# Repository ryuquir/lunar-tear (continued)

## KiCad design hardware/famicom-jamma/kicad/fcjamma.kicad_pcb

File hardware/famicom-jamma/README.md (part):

# ファミコン JAMMA 基板　回路設計（rev 0.3）

日本のファミリーコンピュータ（HVC-001）の CPU（RP2A03）と PPU（RP2C02）を載せ替えて、JAMMA 筐体で動かす基板の設計データです。
調査結果は `reports/ファミコン JAMMA 基板 仕様調査.md`、ユーザー要求は `research_notes/ファミコン JAMMA 基板 仕様調査/user_requirements.md` にあります。

部品の実装はすべて JLCPCB に任せます。自分ではんだ付けする部品はありません。
基板が届いたあとの作業は、ドナー機から外した CPU と PPU をソケットに挿すことと、USB でファームウェアを書くことだけです。

| 版 | 内容 | 場所 |
|---|---|---|
| rev 0.1 | JLCPCB は Basic 部品だけを実装。残りは秋月電子の部品を手はんだ（はんだ付け 約 650 か所） | コミット `35126bd` |
| rev 0.2 | JLCPCB がすべて実装（Extended 部品も使う）。手はんだ 0 か所。独立レビューの前の版 | コミット `ae6575b` |
| **rev 0.3** | **rev 0.2 に独立レビューの指摘を反映した版（6 章）** | この版 |

## 1. 現在の状態

| 段階 | 内容 | 状態 |
|---|---|---|
| 1 | 回路設計（部品の確定、ピン割り当て、回路図、ネットリスト、独立レビュー） | **この版** |
| 2 | フットプリント作成（JAMMA の金フィンガー、60 ピン端子、半固定抵抗など）と部品配置 | **2-1 自作フットプリント: 完了**（`design/footprints.py`。部品用 5 種は 2026-11-15、捨て基板のミシン目と治具穴は 2026-11-16）。**2-2a 基板の外形・捨て基板・取り付け穴・位置合わせマーク・基板の設定: 完了**（`design/board.py` → `kicad/fcjamma.kicad_pcb`、2026-11-16。レビューを受けて同日修正）。2-2b 部品の配置: カセット端子のサンプルと JLCPCB の回答を待つ（配置の案は `mech/board_outline_plan.png`） |
| 3 | 配線、DRC、JLCPCB 向けの製造データ（ガーバー、部品表、座標） | 未着手 |
| 4 | ファームウェア（Pico 2 ×3） | 未着手 |

この版は机上の設計です。実物での動作確認はまだ 1 つもありません。未実証の点は 7 章にまとめています。
段階 3 が終わるまで、この基板は発注できません。
段階 2 の部品配置（2-2）を始める前に済ませることが 2 つあります（8 章）。カセット端子のサンプルでの勘合確認と、JLCPCB への事前質問です。
どちらも依頼者が承認し（2026-11-14）、発注代行（GrokBOT）に頼む文書を Google ドライブの「異能ソフト／ファミコンアーキテクチャー基盤」に置いています。
その結果に左右されない自作フットプリント（2-1）は先に作りました。寸法と出典は `research_notes/ファミコン JAMMA 基板 仕様調査/footprint_specs.md` にあります。
マイコンは Pico 2 のまま進めます（2026-11-15 に決定）。素のチップ（RP2350）に替える案は、調べた結果を `research_notes/ファミコン JAMMA 基板 仕様調査/rp2350_bare_chip_feasibility.md` に残し、次の版で改めて検討します。

## 2. ファイルと作り方

| 場所 | 内容 |
|---|---|
| `design/circuit.py` | 回路の記述（部品、ネット、定数、設計意図の注記）。**これが正本** |
| `design/symbols.py` | KiCad 標準ライブラリにない部品の記号（ピン番号と名前） |
| `design/footprints.py` | 基板の自作フットプリント 7 種（部品用 5 種と、捨て基板のミシン目・治具穴。寸法と出典、ビルドが確かめる事実）と基板の規則。`kicad/fcjamma.pretty` と `kicad/fcjamma.kicad_dru` はここから作る |
| `tools/build.py` | 回路の記述から KiCad プロジェクトを作り、検査し、費用を計算する |
| `tools/jlc_parts.py` | Extended 部品の在庫・価格・実装区分・X 線検査の要否を JLCPCB から取り直す |
| `tools/check_footprints.py` | 自作フットプリントを KiCad 自身（システムの Python の pcbnew）に読ませ、生成器が書いたとおりに読めるか（パッドの位置・大きさ・形・角度・穴・層、禁止域の層と規則、図形と文字の位置、属性）を確かめる（`build.py` が呼ぶ） |
| `tools/check_rules.py` | 基板の規則（`kicad/fcjamma.kicad_dru`）が効くことを試験用の基板で確かめる。禁止の場所に置いた 21 個の試し（ビア、線、パッド、マスクの開口、シルク、小さな部品、穴どうしの間隔、環幅、SMD のパッドの間隔、外形線の無い部品）がそれぞれの規則に引っかかること（規則ごとに 1 つ以上。値のある規則は限界のすぐ内側の試しに引っかかり、すぐ外側の 5 個には引っかからない。値を緩めても厳しくしても分かる）、回路と基板が使う 42 種のフットプリントを 1 つずつ、回路のネットを付けて並べた基板は規則に 1 つも触れないこと（`build.py` が呼ぶ） |
| `tools/fcgen/` | 生成器（回路モデル、部品ヘルパー、KiCad 出力） |
| `tools/setup_env.sh` | 作業環境の準備（KiCad 10 と Python 環境） |
| `data/jlcpcb_basic_parts_2026-11-10.csv` | JLCPCB の Basic 部品 351 件 |
| `data/jlcpcb_extended_parts.csv` | この基板が使う Extended 部品 18 種の在庫・価格・実装区分（取得日つき） |
| `kicad/` | 生成された KiCad 10 プロジェクト（手で編集しない）。ビルドは作業用のフォルダでプロジェクト全体（回路図、記号、フットプリント、基板の規則、基板）を作って検査し、基板も含めてすべて通ったときだけ、生成したファイルを `kicad/` で入れ替える（KiCad の設定・履歴（`.history`）・自動保存などのファイルや、生成していないファイルには触らない）。通らなかったときは `kicad/` と `out/board/` は前に通ったままで、通らなかったプロジェクトは `out/failed/kicad/` に残る。pcbnew が無くて基板を検査できなかったときも `kicad/` は変えず、プロジェクトは `out/unchecked/kicad/` に残る（どちらも git には入れない） |
| `out/` | 回路図 PDF、ネットリスト、部品表、ERC の結果、費用の内訳（`cost_estimate.csv`）。`out/board/` を除き、通らなかったビルドでもそのビルドの内容に書き直される（そのときは `out/failed/kicad/` と合い、`kicad/` とは合わない）。`ordering/make_grok_package.py` は、`out/failed/` か `out/unchecked/` があると止まる |
| `out/footprints/` | 自作フットプリントの図（SVG）と一覧の画像（`footprints_overview.png`）、カセット端子の実寸の確認用紙（`J8_cartridge_slot_1to1_check.pdf`、A4 横、倍率 100 % で印刷） |
| `mech/` | 基板の外形と部品配置の案（`floorplan.py` が重なりを検査してから図を描く）。寸法は `design/board.py` と同じであることをビルドが確かめる |
| `design/board.py` | 基板そのもの（外形、JAMMA のタングとキー溝、捨て基板とミシン目、取り付け穴、治具穴、位置合わせマーク、積層、原点、出力の設定）。`kicad/fcjamma.kicad_pcb` はここから作る |
| `tools/make_board.py` | `design/board.py` から KiCad の基板ファイルを作り、読み直して実測する（タングとキー溝の寸法と位置、タングの横に基板が無いこと、外形の角と溝の形、フィンガーの範囲、J1 の全ピンのネットと回路図とのつながり、穴、捨て基板・つなぎ・ミシン目、治具穴、位置合わせマーク、外形線の有無、積層、出力の設定、縁から部品までの距離など 142 項目。限界値はコネクタの図面と JLCPCB の値を書き直したもの。`build.py` がシステムの Python で呼び、作業用のフォルダのプロジェクトの中で DRC と回路図との照合までかける。ビルド全体が通ったときだけ、プロジェクトごと `kicad/` に入る） |
| `out/board/` | 基板の図（`fcjamma_board.svg`）、上から見た 3D の絵（`fcjamma_board_top.png`）、DRC と回路図との照合の結果（`drc.json`。配線の残りはネットごと、まだ置いていない部品は一覧） |
| `ordering/` | 発注代行（GrokBOT）向けの文書の原稿。`owner_memo.txt`（持ち主用の渡し方のメモ）、`grok_instruction.html`（Grok が最初に読む指示書）、`grok_ordering_knowhow.html`（発注のノウハウとバグチェック）、`jlcpcb_support_question.txt`（JLCPCB への質問文）、`jlcpcb_question_guide.html`（その質問の手引き。質問ごとに何を・なぜ聞くか、十分な答え、聞き直しの決まった英文、報告の形）、`make_grok_package.py`（Google ドライブに上げる一式を作る） |

```
sudo tools/setup_env.sh                      # 初回のみ
python3 tools/jlc_parts.py                   # 発注の直前に。在庫と価格を取り直す
/opt/fcjamma-venv/bin/python tools/build.py  # kicad/ と out/ を作り直して検査する
```

`build.py` は次を検査し、1 つでも外れると失敗します。

- 実装する部品がすべて JLCPCB の部品ライブラリにあること。Basic 部品は Basic の一覧、Extended 部品は `data/jlcpcb_extended_parts.csv` と照合します。
- 部品番号が回路の意図した品名・パッケージと一致すること。
- Extended 部品が Standard PCBA で実装でき、5 枚分以上の在庫があること（20 枚分を切ると警告）。
- 手はんだが必要な部品が 1 つもないこと。
- 標準フットプリントが KiCad のライブラリにあり、記号のピンすべてにパッドがあり、JLCPCB が供給するパッケージと一致すること。パッケージ名で照合できない部品（スイッチ、ソケット、USB 端子）は、メーカーの図面と手で照合済みの組み合わせだけを通す。
- 自作フットプリント（`design/footprints.py`）が、記号のピンすべてにパッドを持ち、描いた対象の部品（JLCPCB の品番）にだけ使われていること。メーカー図面や規格から書き起こした事実（全パッドの位置と大きさ、番号の並び、穴、マスクの開口、禁止域の層と規則、シルクの太さと文字の高さ、写した KiCad ライブラリが確かめた版のままであることなど 28 項目）が成り立つこと。KiCad が、生成器が書いたとおりに読めること。基板の規則（`kicad/fcjamma.kicad_dru`）が、禁止の場所に置いた試しをすべて報告し、限界のすぐ外側の試しは報告しないこと。回路と基板が使うフットプリント 42 種が、どの規則にも触れないこと。
- 基板（`kicad/fcjamma.kicad_pcb`）が 142 項目の実測を通ること。KiCad の DRC の違反が 0 件で、回路図との照合（schematic parity）で食い違いが無いこと（まだ置いていない部品を除く）。配置の案（`mech/floorplan.py`）が基板と同じ寸法で、自分の検査を通ること。新しいプロジェクト（基板、回路図、フットプリント、規則）は、ビルド全体が通ったときだけ `kicad/` に入る（通らなければ `kicad/` と `out/board/` は前に通ったままで、通らなかったプロジェクトは `out/failed/kicad/` に残る。`out/` のほかのファイルは、そのビルドの内容に書き直される）。
- KiCad の電気的規則チェック（ERC）でエラーがないこと。
- KiCad が書き出したネットリストが、回路の記述と 1 ピンずつ一致すること。
- この基板固有の規則 6 つ。
  - ピンが 1 本しか無いネットが無い（ネット名の打ち間違いの検出）。
  - 3.3V 系の外にある部品は、抵抗を通してしか Pico の GPIO につながない（出荷時につながっているはんだジャンパは 1 本の線として扱う）。GPIO を抵抗で 5V の電源へ直接つないでいない。
  - IC ごとに、その IC 専用の 100 nF がある。
  - バスの各ビットの接続が揃っていて、決まった本数がすべてある（データバス、ダンプ回路の直列抵抗など 10 系統）。
  - 同じ IC の駆動端子が 2 本、同じネットにつながっていない。
  - 5V を受けられない GPIO26〜28 は、5V になりうる線から抵抗で受けるとき、実装される GND への抵抗を持ち、相手が 5.5V のときも端子が 3.3V 以下になる。
- 極性やピン番号を誤ると検査をすり抜ける部品（電源スイッチ、レギュレータ、TVS、ダイオード、LED、MOSFET 7 個、PNP、半固定抵抗、比較器、有極コンデンサ、クロックのジャンパ、ダンプ回路の許可回路の各部品）について、データシートから書き起こした事実が成り立つこと（`design/circuit.py` の `selfcheck`）。

回路図は「部品とネット名のラベル」だけで描いています（配線は引いていません）。同じ名前のラベルがつながっています。

## 3. 回路の概要

### 3.1 2 つの動作モード

| モード | CPU・PPU のソケット | DIP スイッチ 1 番 | しくみ |
|---|---|---|---|
| 実チップ | ドナー機の RP2A03 と RP2C02 を挿す | OFF | カセットを実機と同じ回路で動かす。映像は PPU の EXT 端子から色番号を取り出して RGB にする |
| エミュレーション | 空にする | ON | Pico C がカセットの中身を読み出し、Pico A がエミュレータを動かす |

Pico 2 は 3 枚とも基板にはんだ付けされていて、どちらのモードでも使います。CPU・PPU と Pico を同じソケットで差し替える形にはしていません（ピン配置も電圧も合わないため）。

チップを挿したまま DIP スイッチを ON にしてしまっても壊れないように、三重に守っています（3.6 節）。

### 3.2 Pico 2 の役割とピン

| 枚 | 役割 |
|---|---|
| A（映像） | CPU・PPU のクロック（21.5 MHz）とリセット。EXT0〜3 とスプライト判定ビットの取り込み。RGB と同期の出力。重ね表示。エミュレーションモードではエミュレータ本体と音声 |
| B（バス） | CPU が PPU のレジスタに書く値の監視。パレット値などを PPU の手前で差し替え。パッド読み出し（$4016・$4017）への応答 |
| C（入出力・管理） | JAMMA の入力と出力、コインとタイマー、カセットの読み出し、USB Type-C、Famicom 側の電源スイッチ、音声アンプの入り切り、A と B のリセットと書き換え |

| GPIO | Pico A | Pico B | Pico C |
|---|---|---|---|
| 0 | EXT0（入力） | CPU 側 D0 | ダンプ SER |
| 1 | EXT1 | CPU 側 D1 | ダンプ 高速シフトクロック |
| 2 | EXT2 | CPU 側 D2 | ダンプ 低速シフトクロック |
| 3 | EXT3 | CPU 側 D3 | ダンプ ラッチ |
| 4 | スプライト判定ビット | CPU 側 D4 | ダンプ回路の許可（High で許可。DIP 1 番が ON のときだけ効く） |
| 5 | ALE | CPU 側 D5 | 予備（テストパッド `C_SPARE`） |
| 6 | R0 | CPU 側 D6 | M2 の監視（入力のみ） |
| 7 | R1 | CPU 側 D7 | JAMMA 出力の許可（Low で有効） |
| 8 | R2 | PPU 側 D0（差し替え出力） | 入力チェーンのデータ |
| 9 | G0 | PPU 側 D1 | 入出力チェーンのラッチ |
| 10 | G1 | PPU 側 D2 | 入出力チェーンのクロック |
| 11 | G2 | PPU 側 D3 | 出力チェーンのデータ |
| 12 | G3 | PPU 側 D4 | Pico A の SWCLK |
| 13 | B0 | PPU 側 D5 | Pico A の SWDIO |
| 14 | B1 | PPU 側 D6 | Pico B の SWCLK |
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
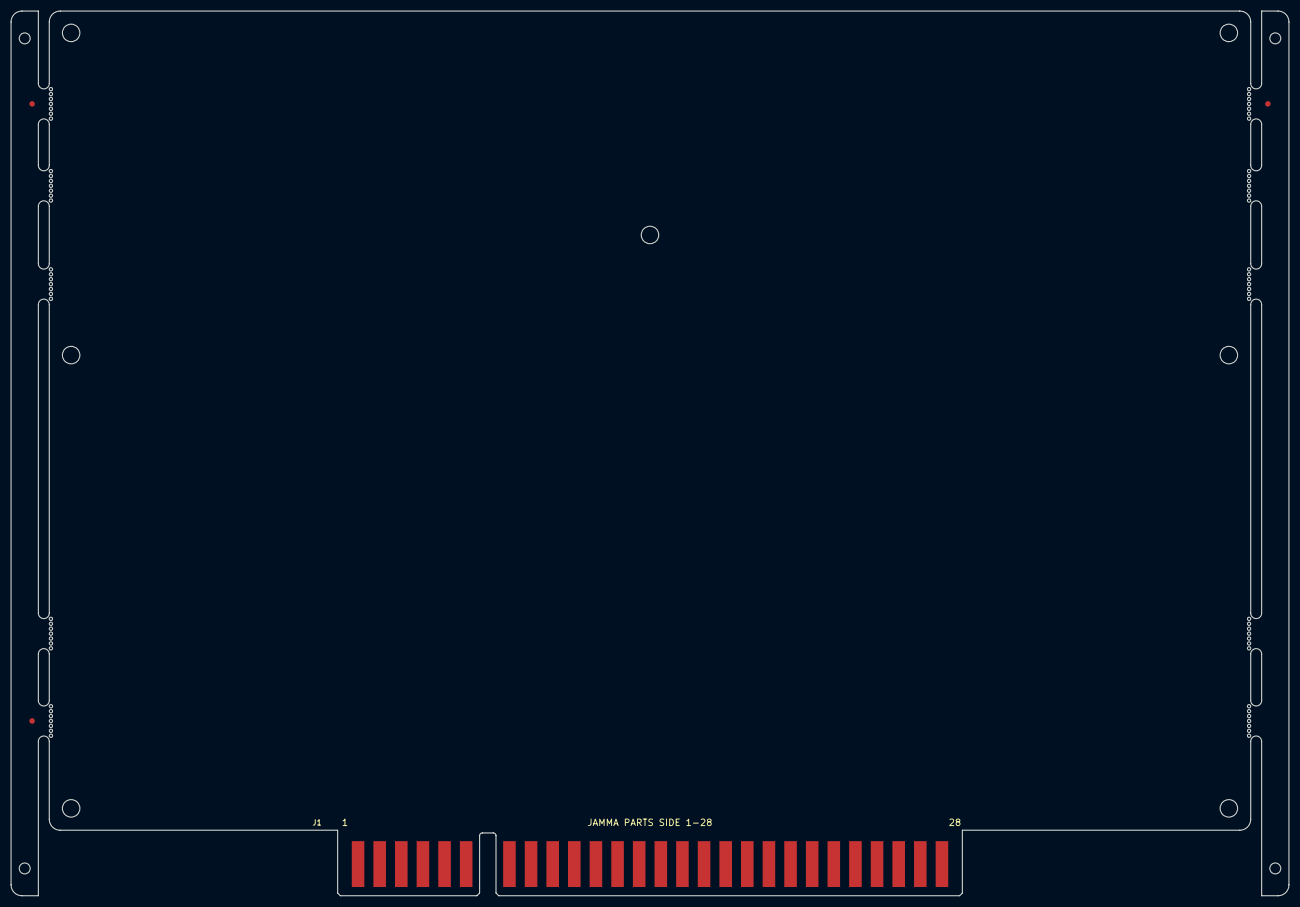
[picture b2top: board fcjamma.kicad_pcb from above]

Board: 2 copper layers, 234.0 x 162.0 mm, 25 parts (0 on the bottom side), 2 nets, no tracks yet.

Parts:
FID1, FID2, FID3: Fiducial; Fiducial_1mm_Mask2mm
H1, H2, H3, H4, H5, H6, H7: M3; MountingHole_3.2mm_M3
J1: JAMMA edge (gold fingers); JAMMA_Edge_56
MB1, MB2, MB3, MB4, MB5, MB6, MB7, MB8, MB9, MB10: Mouse bites; BreakLine_7h_D0.6mm_P0.9mm_KeepOut
TH1, TH2, TH3, TH4: Tooling hole; ToolingHole_2.0mm_NPTH

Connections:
+5V_IN: J1.3, J1.4, J1.C, J1.D
GND: J1.1, J1.2, J1.14, J1.27, J1.28, J1.A, J1.B, J1.e, J1.f

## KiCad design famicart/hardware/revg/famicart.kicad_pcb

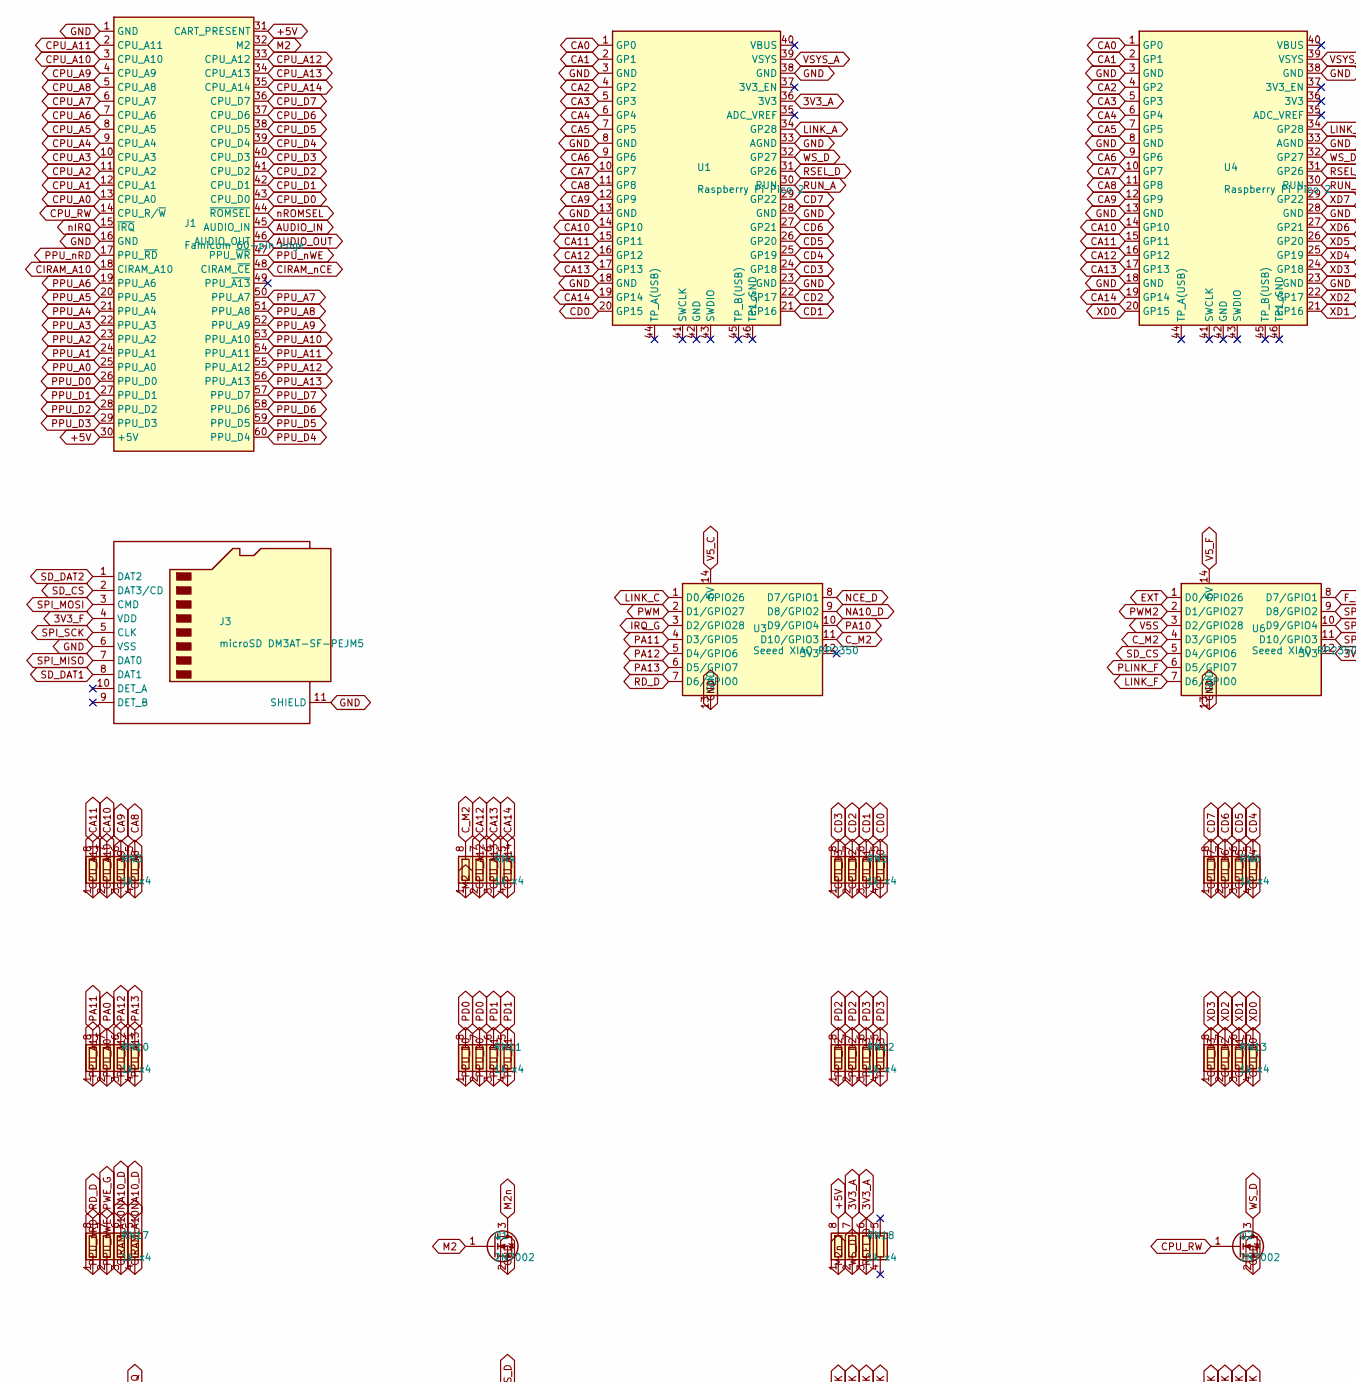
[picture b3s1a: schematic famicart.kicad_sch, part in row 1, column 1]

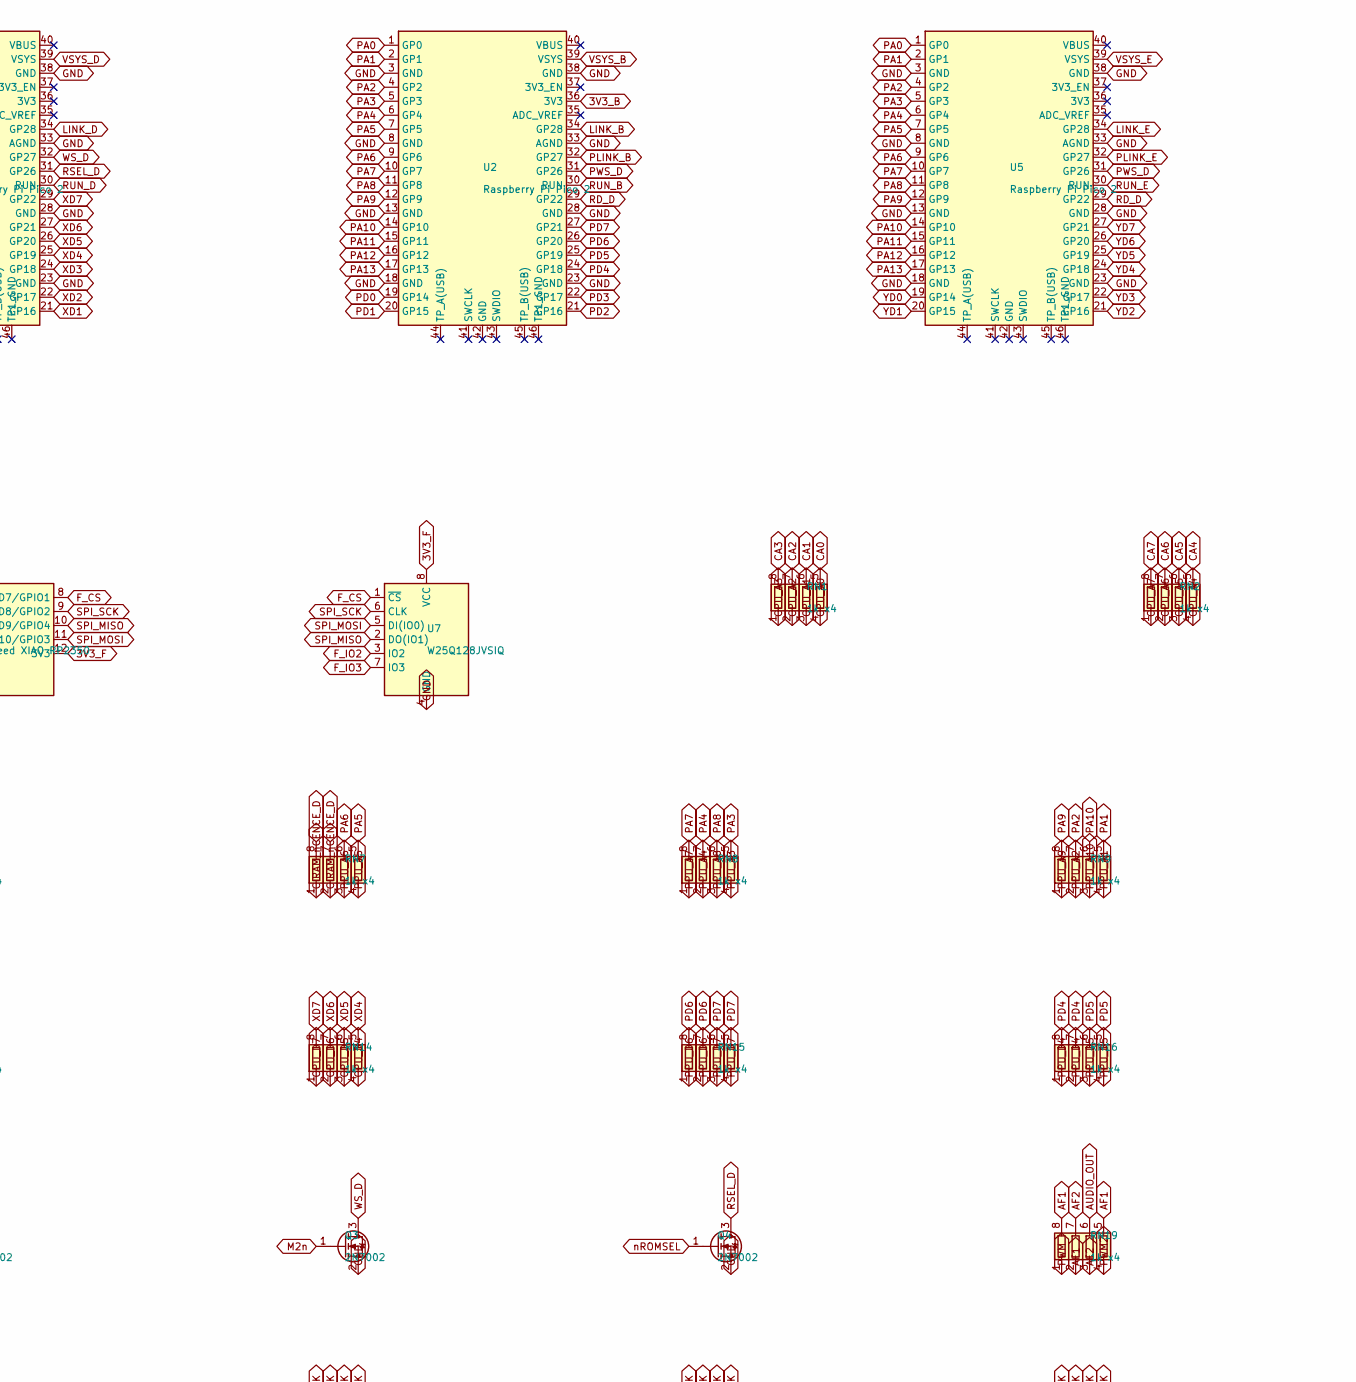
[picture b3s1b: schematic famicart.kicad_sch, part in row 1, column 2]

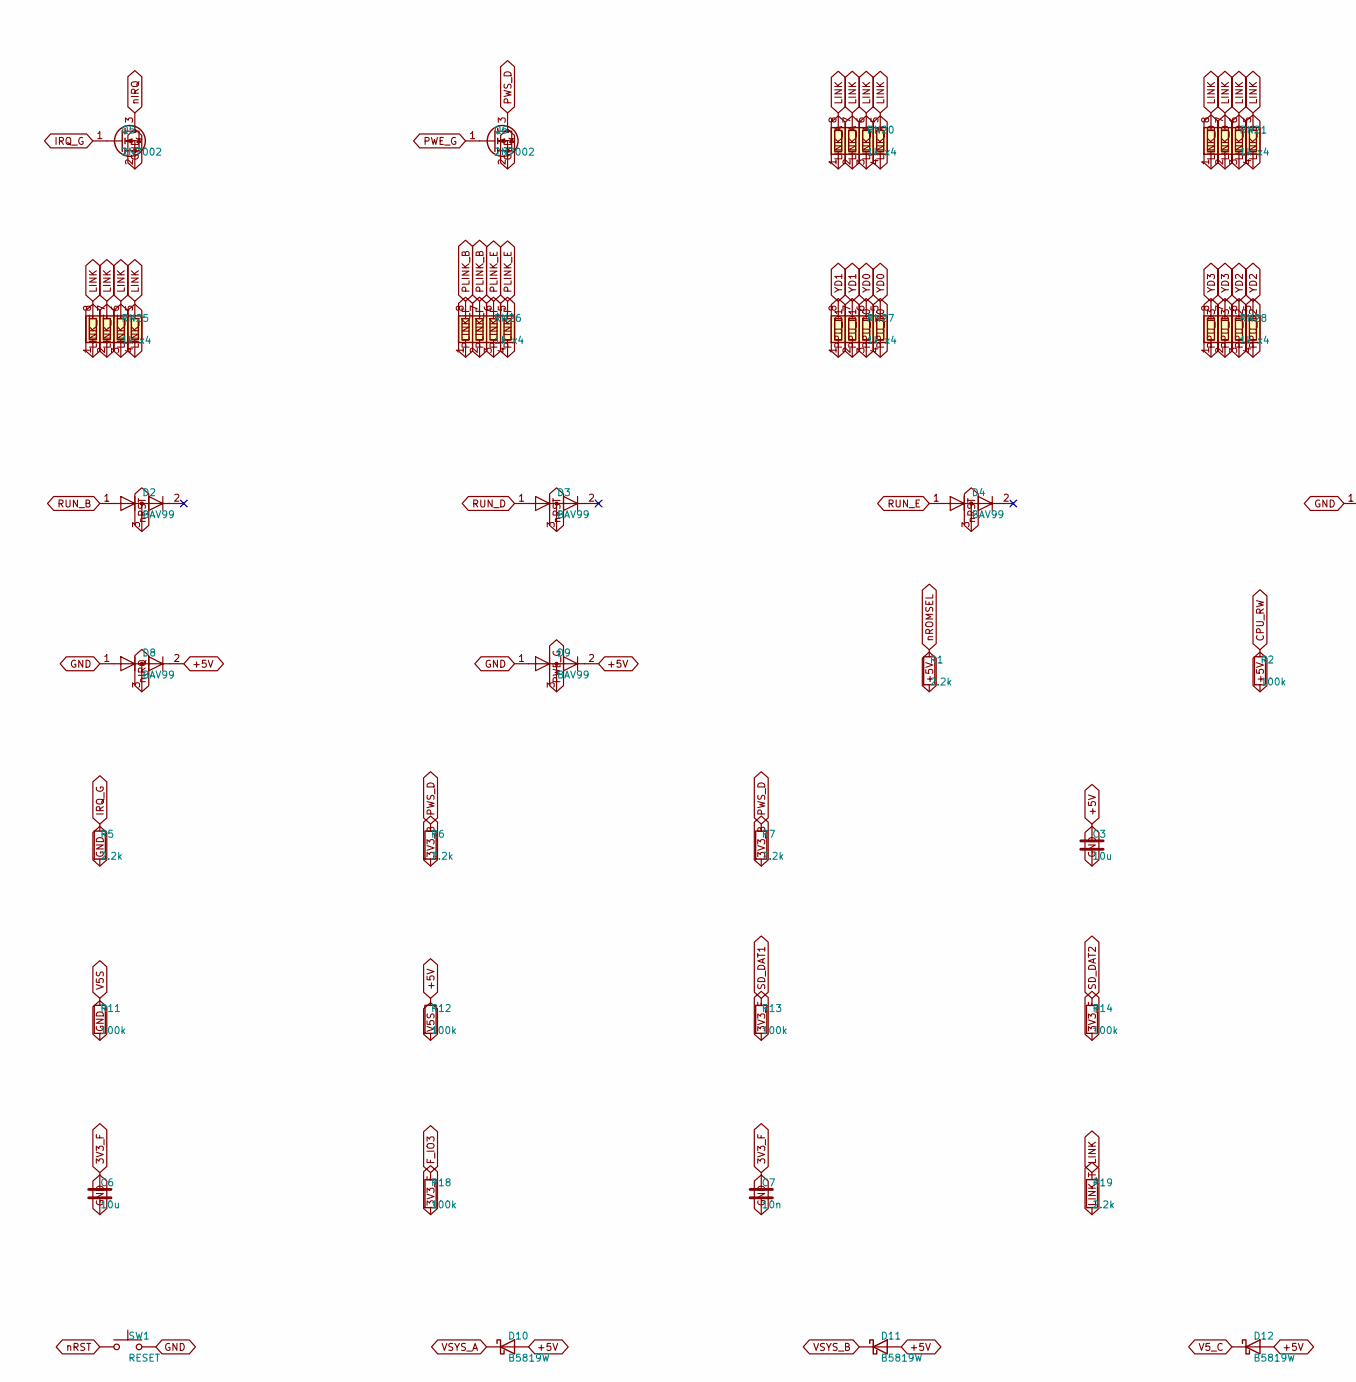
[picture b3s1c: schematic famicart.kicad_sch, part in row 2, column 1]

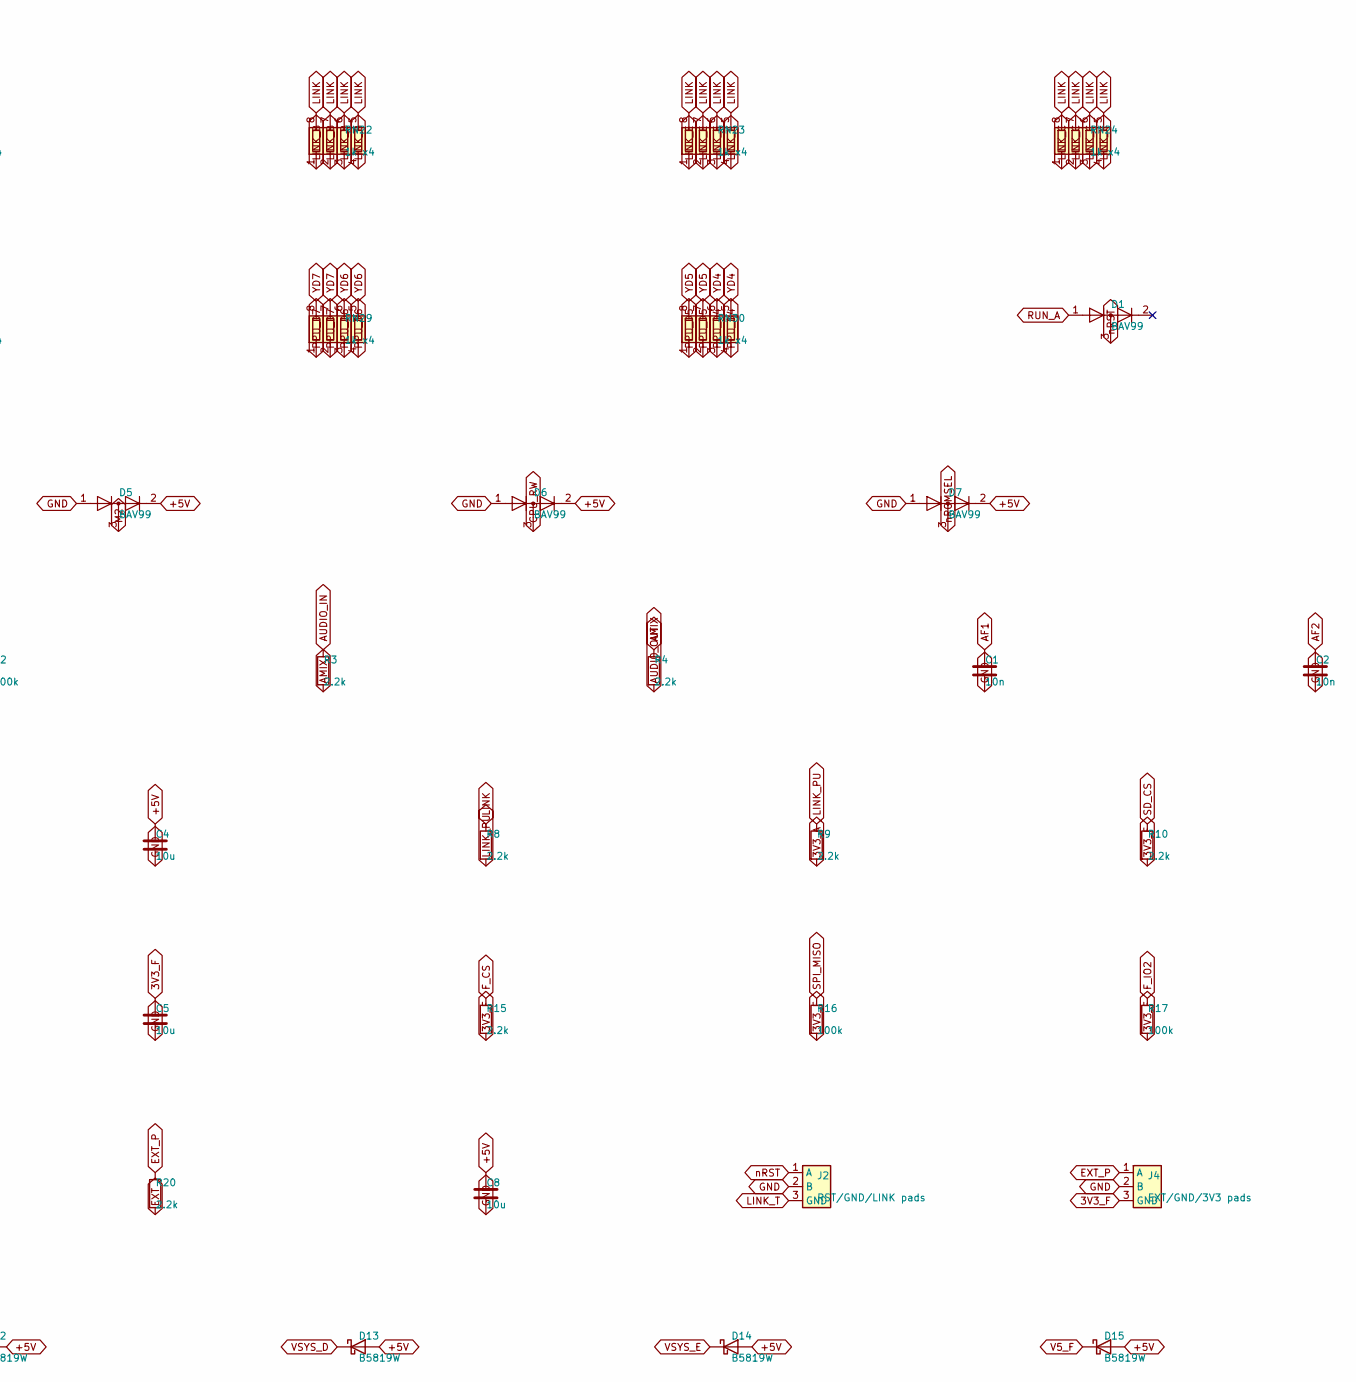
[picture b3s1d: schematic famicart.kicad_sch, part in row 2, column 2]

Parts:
C1, C2, C7: 10n; C_0603_1608Metric
C3, C4, C5, C6, C8: 10u; C_0805_2012Metric
D1, D2, D3, D4, D5, D6, D7, D8, D9: BAV99; SOT-23
D10, D11, D12, D13, D14, D15: B5819W; D_SOD-123
J1: Famicom 60-pin edge; Famicom_CardEdge_60
J2: RST/GND/LINK pads; WirePads_1x3
J3: microSD DM3AT-SF-PEJM5; microSD_HC_Hirose_DM3AT-SF-PEJM5
J4: EXT/GND/3V3 pads; WirePads_1x3
Q1, Q2, Q3, Q4, Q5, Q6: 2N7002; SOT-23
R1, R3, R4, R5, R6, R7, R8, R9, R10, R15, R19, R20: 2.2k; R_0603_1608Metric
R2, R11, R12, R13, R14, R16, R17, R18: 100k; R_0603_1608Metric
RN1, RN2, RN3, RN4, RN5, RN6, RN7, RN8, RN9, RN10, RN11, RN12, RN13, RN14, RN15, RN16, RN17, RN18, RN19, RN20, RN21, RN22, RN23, RN24, RN25, RN26, RN27, RN28, RN29, RN30: 1k x4; R_Array_Convex_4x0603
SW1: RESET; SW_Push_1P1T_XKB_TS-1187A
U1, U2, U4, U5: Raspberry Pi Pico 2; RPi_Pico_SMD_Short
U3, U6: Seeed XIAO RP2350; XIAO-RP2350-Edge
U7: W25Q128JVSIQ; SOIC-8_5.23x5.23mm_P1.27mm

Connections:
3V3_A: R9.2, RN18.6 (R3.2), RN18.7 (R2.2), U1.36 (3V3)
3V3_B: R6.2, R7.2, U2.36 (3V3)
3V3_F: C5.1, C6.1, C7.1, J3.4 (VDD), J4.3 (GND), R10.2, R13.2, R14.2, R15.2, R16.2, R17.2, R18.2, U6.12 (3V3), U7.8 (VCC)
+5V: C3.1, C4.1, C8.1, D5.2 (A), D6.2 (A), D7.2 (A), D8.2 (A), D9.2 (A), D10.2 (A), D11.2 (A), D12.2 (A), D13.2 (A), D14.2 (A), D15.2 (A), J1.30 (+5V), J1.31 (CART_PRESENT), R1.2, R2.2, R12.1, RN18.8 (R1.2)
AF1: C1.1, RN19.2 (R2.1), RN19.5 (R4.2), RN19.8 (R1.2)
AF2: C2.1, RN19.3 (R3.1), RN19.7 (R2.2)
AMIX: R3.2, R4.1
AUDIO_IN: J1.45 (AUDIO_IN), R3.1
AUDIO_OUT: J1.46 (AUDIO_OUT), R4.2, RN19.6 (R3.2)
CA0: RN1.5 (R4.2), U1.1 (GP0), U4.1 (GP0)
CA1: RN1.6 (R3.2), U1.2 (GP1), U4.2 (GP1)
CA2: RN1.7 (R2.2), U1.4 (GP2), U4.4 (GP2)
CA3: RN1.8 (R1.2), U1.5 (GP3), U4.5 (GP3)
CA4: RN2.5 (R4.2), U1.6 (GP4), U4.6 (GP4)
CA5: RN2.6 (R3.2), U1.7 (GP5), U4.7 (GP5)
CA6: RN2.7 (R2.2), U1.9 (GP6), U4.9 (GP6)
CA7: RN2.8 (R1.2), U1.10 (GP7), U4.10 (GP7)
CA8: RN3.5 (R4.2), U1.11 (GP8), U4.11 (GP8)
CA9: RN3.6 (R3.2), U1.12 (GP9), U4.12 (GP9)
CA10: RN3.7 (R2.2), U1.14 (GP10), U4.14 (GP10)
CA11: RN3.8 (R1.2), U1.15 (GP11), U4.15 (GP11)
CA12: RN4.7 (R2.2), U1.16 (GP12), U4.16 (GP12)
CA13: RN4.6 (R3.2), U1.17 (GP13), U4.17 (GP13)
CA14: RN4.5 (R4.2), U1.19 (GP14), U4.19 (GP14)
CD0: RN5.5 (R4.2), U1.20 (GP15)
CD1: RN5.6 (R3.2), U1.21 (GP16)
CD2: RN5.7 (R2.2), U1.22 (GP17)
CD3: RN5.8 (R1.2), U1.24 (GP18)
CD4: RN6.5 (R4.2), U1.25 (GP19)
CD5: RN6.6 (R3.2), U1.26 (GP20)
CD6: RN6.7 (R2.2), U1.27 (GP21)
CD7: RN6.8 (R1.2), U1.29 (GP22)
CIRAM_A10: J1.18 (CIRAM_A10), RN17.3 (R3.1), RN17.4 (R4.1)
CIRAM_nCE: J1.48 (CIRAM_~CE), RN7.1 (R1.1), RN7.2 (R2.1)
CPU_A0: J1.13 (CPU_A0), RN1.4 (R4.1)
CPU_A1: J1.12 (CPU_A1), RN1.3 (R3.1)
CPU_A2: J1.11 (CPU_A2), RN1.2 (R2.1)
CPU_A3: J1.10 (CPU_A3), RN1.1 (R1.1)
CPU_A4: J1.9 (CPU_A4), RN2.4 (R4.1)
CPU_A5: J1.8 (CPU_A5), RN2.3 (R3.1)
CPU_A6: J1.7 (CPU_A6), RN2.2 (R2.1)
CPU_A7: J1.6 (CPU_A7), RN2.1 (R1.1)
CPU_A8: J1.5 (CPU_A8), RN3.4 (R4.1)
CPU_A9: J1.4 (CPU_A9), RN3.3 (R3.1)
CPU_A10: J1.3 (CPU_A10), RN3.2 (R2.1)
CPU_A11: J1.2 (CPU_A11), RN3.1 (R1.1)
CPU_A12: J1.33 (CPU_A12), RN4.2 (R2.1)
CPU_A13: J1.34 (CPU_A13), RN4.3 (R3.1)
CPU_A14: J1.35 (CPU_A14), RN4.4 (R4.1)
CPU_D0: J1.43 (CPU_D0), RN5.4 (R4.1), RN13.4 (R4.1)
CPU_D1: J1.42 (CPU_D1), RN5.3 (R3.1), RN13.3 (R3.1)
CPU_D2: J1.41 (CPU_D2), RN5.2 (R2.1), RN13.2 (R2.1)
CPU_D3: J1.40 (CPU_D3), RN5.1 (R1.1), RN13.1 (R1.1)
CPU_D4: J1.39 (CPU_D4), RN6.4 (R4.1), RN14.4 (R4.1)
CPU_D5: J1.38 (CPU_D5), RN6.3 (R3.1), RN14.3 (R3.1)
CPU_D6: J1.37 (CPU_D6), RN6.2 (R2.1), RN14.2 (R2.1)
CPU_D7: J1.36 (CPU_D7), RN6.1 (R1.1), RN14.1 (R1.1)
CPU_RW: D6.3 (K), J1.14 (CPU_R/~W), Q2.1 (G), R2.1
C_M2: RN4.8 (R1.2), U3.11 (D10/GPIO3), U6.4 (D3/GPIO5)
EXT: R20.2, U6.1 (D0/GPIO26)
EXT_P: J4.1 (A), R20.1
F_CS: R15.1, U6.8 (D7/GPIO1), U7.1 (~CS)
F_IO2: R17.1, U7.3 (IO2)
F_IO3: R18.1, U7.7 (IO3)
GND: C1.2, C2.2, C3.2, C4.2, C5.2, C6.2, C7.2, C8.2, D5.1 (K), D6.1 (K), D7.1 (K), D8.1 (K), D9.1 (K), J1.1 (GND), J1.16 (GND), J2.2 (B), J3.6 (VSS), J3.11 (SHIELD), J4.2 (B), Q1.2 (S), Q2.2 (S), Q3.2 (S), Q4.2 (S), Q5.2 (S), Q6.2 (S), R5.2, R11.2, SW1.2, U1.3 (GND), U1.8 (GND), U1.13 (GND), U1.18 (GND), U1.23 (GND), U1.28 (GND), U1.33 (AGND), U1.38 (GND), U2.3 (GND), U2.8 (GND), U2.13 (GND), U2.18 (GND), U2.23 (GND), U2.28 (GND), U2.33 (AGND), U2.38 (GND), U3.13 (GND), U4.3 (GND), U4.8 (GND), U4.13 (GND), U4.18 (GND), U4.23 (GND), U4.28 (GND), U4.33 (AGND), U4.38 (GND), U5.3 (GND), U5.8 (GND), U5.13 (GND), U5.18 (GND), U5.23 (GND), U5.28 (GND), U5.33 (AGND), U5.38 (GND), U6.13 (GND), U7.4 (GND)
IRQ_G: Q5.1 (G), R5.1, U3.3 (D2/GPIO28)
LINK: R8.1, R19.1, RN20.5 (R4.2), RN20.6 (R3.2), RN20.7 (R2.2), RN20.8 (R1.2), RN21.5 (R4.2), RN21.6 (R3.2), RN21.7 (R2.2), RN21.8 (R1.2), RN22.5 (R4.2), RN22.6 (R3.2), RN22.7 (R2.2), RN22.8 (R1.2), RN23.5 (R4.2), RN23.6 (R3.2), RN23.7 (R2.2), RN23.8 (R1.2), RN24.5 (R4.2), RN24.6 (R3.2), RN24.7 (R2.2), RN24.8 (R1.2), RN25.5 (R4.2), RN25.6 (R3.2), RN25.7 (R2.2), RN25.8 (R1.2)
LINK_A: RN20.1 (R1.1), RN20.2 (R2.1), RN20.3 (R3.1), RN20.4 (R4.1), U1.34 (GP28)
LINK_B: RN22.1 (R1.1), RN22.2 (R2.1), RN22.3 (R3.1), RN22.4 (R4.1), U2.34 (GP28)
LINK_C: RN24.1 (R1.1), RN24.2 (R2.1), RN24.3 (R3.1), RN24.4 (R4.1), U3.1 (D0/GPIO26)
LINK_D: RN21.1 (R1.1), RN21.2 (R2.1), RN21.3 (R3.1), RN21.4 (R4.1), U4.34 (GP28)
LINK_E: RN23.1 (R1.1), RN23.2 (R2.1), RN23.3 (R3.1), RN23.4 (R4.1), U5.34 (GP28)
LINK_F: RN25.1 (R1.1), RN25.2 (R2.1), RN25.3 (R3.1), RN25.4 (R4.1), U6.7 (D6/GPIO0)
LINK_PU: R8.2, R9.1
LINK_T: J2.3 (GND), R19.2
M2: D5.3 (K), J1.32 (M2), Q1.1 (G), RN4.1 (R1.1)
M2n: Q1.3 (D), Q3.1 (G), RN18.1 (R1.1)
NA10_D: RN17.5 (R4.2), RN17.6 (R3.2), U3.9 (D8/GPIO2)
NCE_D: RN7.7 (R2.2), RN7.8 (R1.2), U3.8 (D7/GPIO1)
PA0: RN10.7 (R2.2), U2.1 (GP0), U5.1 (GP0)
PA1: RN9.5 (R4.2), U2.2 (GP1), U5.2 (GP1)
PA2: RN9.7 (R2.2), U2.4 (GP2), U5.4 (GP2)
PA3: RN8.5 (R4.2), U2.5 (GP3), U5.5 (GP3)
PA4: RN8.7 (R2.2), U2.6 (GP4), U5.6 (GP4)
PA5: RN7.5 (R4.2), U2.7 (GP5), U5.7 (GP5)
PA6: RN7.6 (R3.2), U2.9 (GP6), U5.9 (GP6)
PA7: RN8.8 (R1.2), U2.10 (GP7), U5.10 (GP7)
PA8: RN8.6 (R3.2), U2.11 (GP8), U5.11 (GP8)
PA9: RN9.8 (R1.2), U2.12 (GP9), U5.12 (GP9)
PA10: RN9.6 (R3.2), U2.14 (GP10), U3.10 (D9/GPIO4), U5.14 (GP10)
PA11: RN10.8 (R1.2), U2.15 (GP11), U3.4 (D3/GPIO5), U5.15 (GP11)
PA12: RN10.6 (R3.2), U2.16 (GP12), U3.5 (D4/GPIO6), U5.16 (GP12)
PA13: RN10.5 (R4.2), U2.17 (GP13), U3.6 (D5/GPIO7), U5.17 (GP13)
PD0: RN11.7 (R2.2), RN11.8 (R1.2), U2.19 (GP14)
PD1: RN11.5 (R4.2), RN11.6 (R3.2), U2.20 (GP15)
PD2: RN12.7 (R2.2), RN12.8 (R1.2), U2.21 (GP16)
PD3: RN12.5 (R4.2), RN12.6 (R3.2), U2.22 (GP17)
PD4: RN16.7 (R2.2), RN16.8 (R1.2), U2.24 (GP18)
PD5: RN16.5 (R4.2), RN16.6 (R3.2), U2.25 (GP19)
PD6: RN15.7 (R2.2), RN15.8 (R1.2), U2.26 (GP20)
PD7: RN15.5 (R4.2), RN15.6 (R3.2), U2.27 (GP21)
PLINK_B: RN26.7 (R2.2), RN26.8 (R1.2), U2.32 (GP27)
PLINK_E: RN26.5 (R4.2), RN26.6 (R3.2), U5.32 (GP27)
PLINK_F: RN26.1 (R1.1), RN26.2 (R2.1), RN26.3 (R3.1), RN26.4 (R4.1), U6.6 (D5/GPIO7)
PPU_A0: J1.25 (PPU_A0), RN10.2 (R2.1)
PPU_A1: J1.24 (PPU_A1), RN9.4 (R4.1)
PPU_A2: J1.23 (PPU_A2), RN9.2 (R2.1)
PPU_A3: J1.22 (PPU_A3), RN8.4 (R4.1)
PPU_A4: J1.21 (PPU_A4), RN8.2 (R2.1)
PPU_A5: J1.20 (PPU_A5), RN7.4 (R4.1)
PPU_A6: J1.19 (PPU_A6), RN7.3 (R3.1)
PPU_A7: J1.50 (PPU_A7), RN8.1 (R1.1)
PPU_A8: J1.51 (PPU_A8), RN8.3 (R3.1)
PPU_A9: J1.52 (PPU_A9), RN9.1 (R1.1)
PPU_A10: J1.53 (PPU_A10), RN9.3 (R3.1)
PPU_A11: J1.54 (PPU_A11), RN10.1 (R1.1)
PPU_A12: J1.55 (PPU_A12), RN10.3 (R3.1)
PPU_A13: J1.56 (PPU_A13), RN10.4 (R4.1)
PPU_D0: J1.26 (PPU_D0), RN11.1 (R1.1), RN11.2 (R2.1), RN27.3 (R3.1), RN27.4 (R4.1)
PPU_D1: J1.27 (PPU_D1), RN11.3 (R3.1), RN11.4 (R4.1), RN27.1 (R1.1), RN27.2 (R2.1)
PPU_D2: J1.28 (PPU_D2), RN12.1 (R1.1), RN12.2 (R2.1), RN28.3 (R3.1), RN28.4 (R4.1)
PPU_D3: J1.29 (PPU_D3), RN12.3 (R3.1), RN12.4 (R4.1), RN28.1 (R1.1), RN28.2 (R2.1)
PPU_D4: J1.60 (PPU_D4), RN16.1 (R1.1), RN16.2 (R2.1), RN30.3 (R3.1), RN30.4 (R4.1)
PPU_D5: J1.59 (PPU_D5), RN16.3 (R3.1), RN16.4 (R4.1), RN30.1 (R1.1), RN30.2 (R2.1)
PPU_D6: J1.58 (PPU_D6), RN15.1 (R1.1), RN15.2 (R2.1), RN29.3 (R3.1), RN29.4 (R4.1)
PPU_D7: J1.57 (PPU_D7), RN15.3 (R3.1), RN15.4 (R4.1), RN29.1 (R1.1), RN29.2 (R2.1)
PPU_nRD: J1.17 (PPU_~RD), RN17.1 (R1.1)
PPU_nWE: J1.47 (PPU_~WR), RN17.2 (R2.1)
PWE_G: D9.3 (K), Q6.1 (G), RN17.7 (R2.2)
PWM: RN19.1 (R1.1), U3.2 (D1/GPIO27)
PWM2: RN19.4 (R4.1), U6.2 (D1/GPIO27)
PWS_D: Q6.3 (D), R6.1, R7.1, U2.31 (GP26), U5.31 (GP26)
RD_D: RN17.8 (R1.2), U2.29 (GP22), U3.7 (D6/GPIO0), U5.29 (GP22)
RSEL_D: Q4.3 (D), RN18.3 (R3.1), U1.31 (GP26), U4.31 (GP26)
RUN_A: D1.1 (K), U1.30 (RUN)
RUN_B: D2.1 (K), U2.30 (RUN)
RUN_D: D3.1 (K), U4.30 (RUN)
RUN_E: D4.1 (K), U5.30 (RUN)
SD_CS: J3.2 (DAT3/CD), R10.1, U6.5 (D4/GPIO6)
SD_DAT1: J3.8 (DAT1), R13.1
SD_DAT2: J3.1 (DAT2), R14.1
SPI_MISO: J3.7 (DAT0), R16.1, U6.10 (D9/GPIO4), U7.2 (DO(IO1))
SPI_MOSI: J3.3 (CMD), U6.11 (D10/GPIO3), U7.5 (DI(IO0))
SPI_SCK: J3.5 (CLK), U6.9 (D8/GPIO2), U7.6 (CLK)
V5S: R11.1, R12.2, U6.3 (D2/GPIO28)
V5_C: D12.1 (K), U3.14 (5V)
V5_F: D15.1 (K), U6.14 (5V)
VSYS_A: D10.1 (K), U1.39 (VSYS)
VSYS_B: D11.1 (K), U2.39 (VSYS)
VSYS_D: D13.1 (K), U4.39 (VSYS)
VSYS_E: D14.1 (K), U5.39 (VSYS)
WS_D: Q2.3 (D), Q3.3 (D), RN18.2 (R2.1), U1.32 (GP27), U4.32 (GP27)
XD0: RN13.5 (R4.2), U4.20 (GP15)
XD1: RN13.6 (R3.2), U4.21 (GP16)
XD2: RN13.7 (R2.2), U4.22 (GP17)
XD3: RN13.8 (R1.2), U4.24 (GP18)
XD4: RN14.5 (R4.2), U4.25 (GP19)
XD5: RN14.6 (R3.2), U4.26 (GP20)
XD6: RN14.7 (R2.2), U4.27 (GP21)
XD7: RN14.8 (R1.2), U4.29 (GP22)
YD0: RN27.5 (R4.2), RN27.6 (R3.2), U5.19 (GP14)
YD1: RN27.7 (R2.2), RN27.8 (R1.2), U5.20 (GP15)
YD2: RN28.5 (R4.2), RN28.6 (R3.2), U5.21 (GP16)
YD3: RN28.7 (R2.2), RN28.8 (R1.2), U5.22 (GP17)
YD4: RN30.5 (R4.2), RN30.6 (R3.2), U5.24 (GP18)
YD5: RN30.7 (R2.2), RN30.8 (R1.2), U5.25 (GP19)
YD6: RN29.5 (R4.2), RN29.6 (R3.2), U5.26 (GP20)
YD7: RN29.7 (R2.2), RN29.8 (R1.2), U5.27 (GP21)
nIRQ: D8.3 (K), J1.15 (~IRQ), Q5.3 (D)
nROMSEL: D7.3 (K), J1.44 (~ROMSEL), Q4.1 (G), R1.1
nRST: D1.3 (K), D2.3 (K), D3.3 (K), D4.3 (K), J2.1 (A), SW1.1

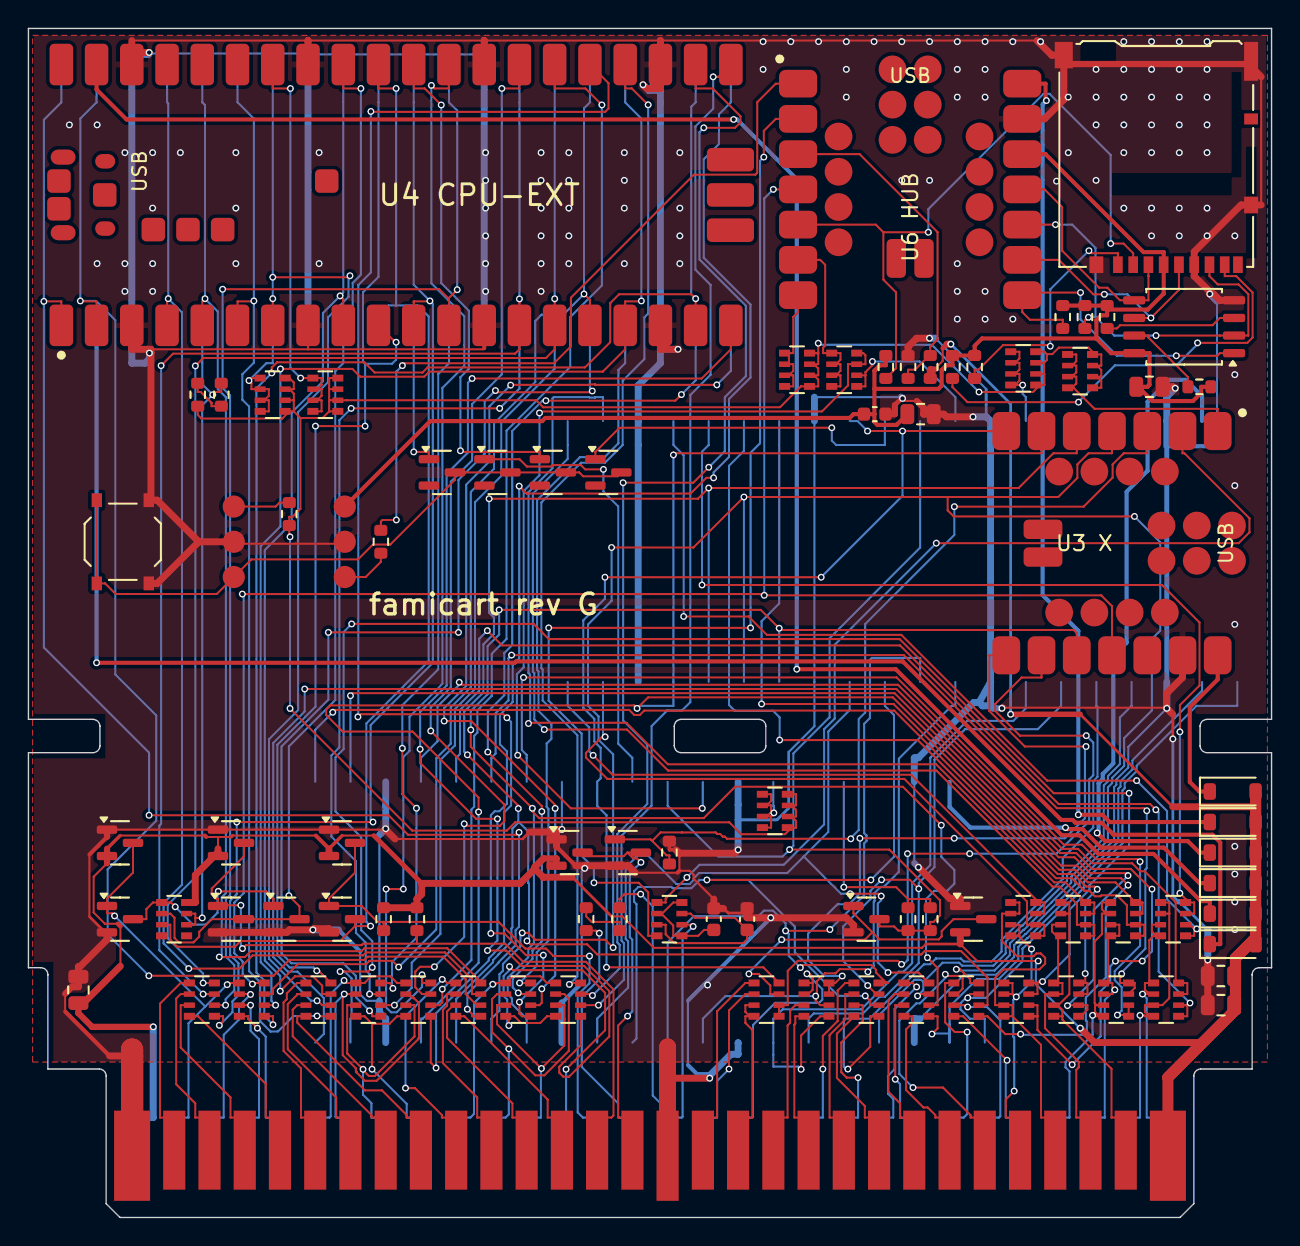
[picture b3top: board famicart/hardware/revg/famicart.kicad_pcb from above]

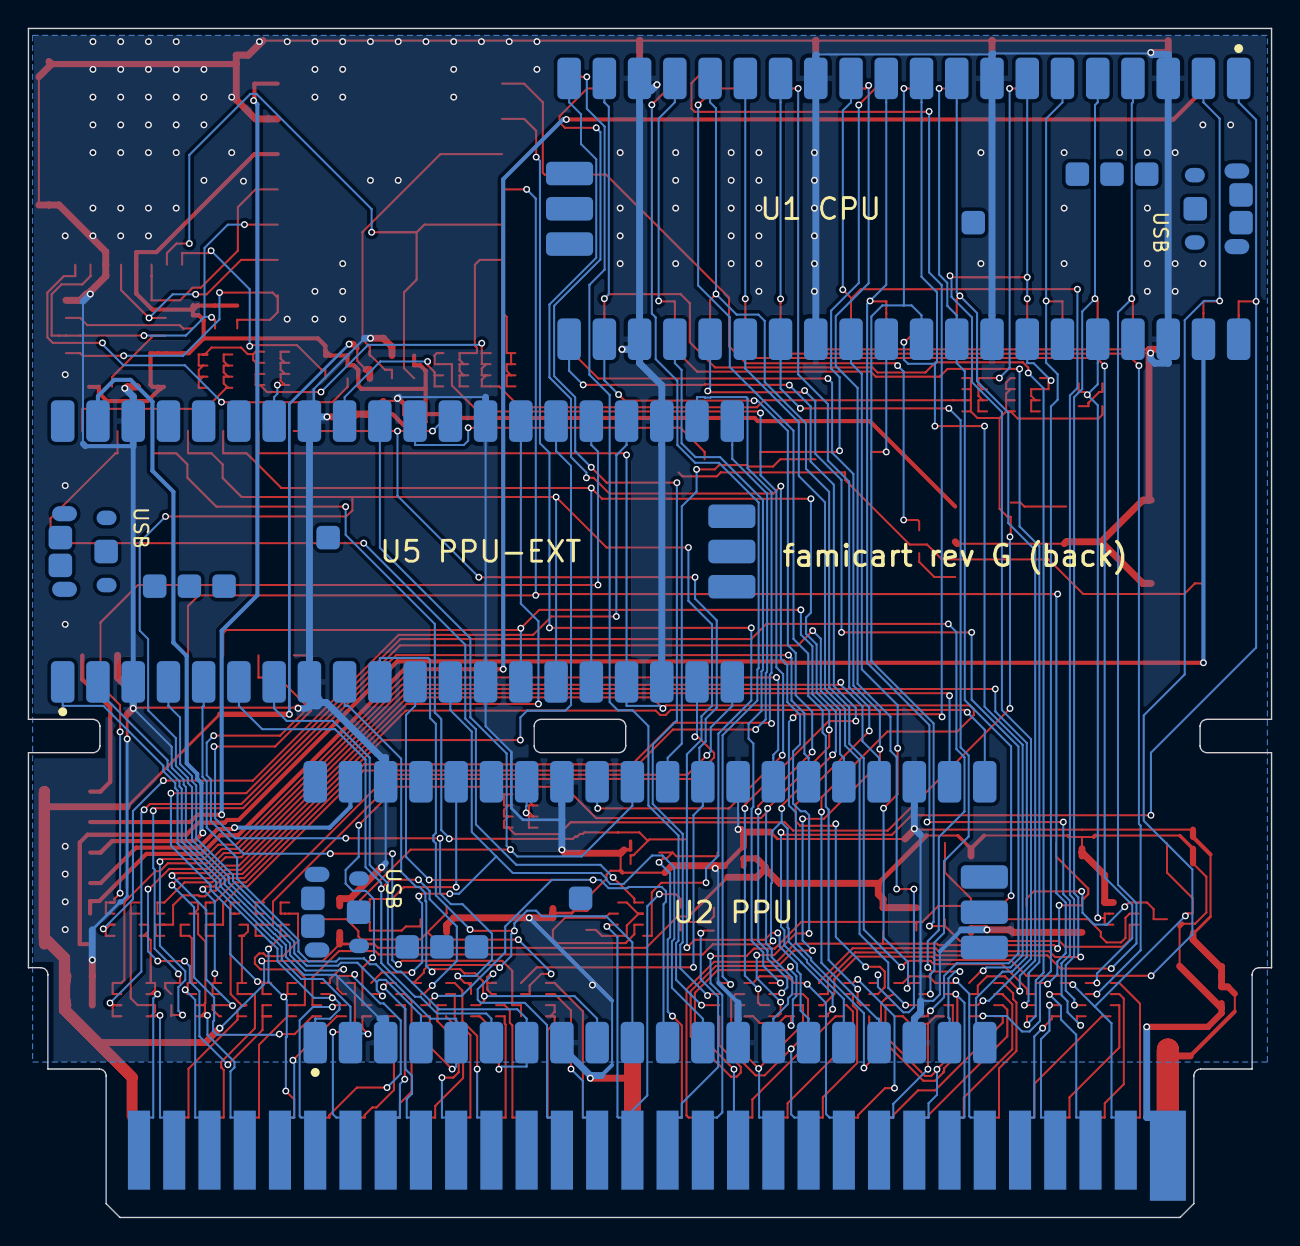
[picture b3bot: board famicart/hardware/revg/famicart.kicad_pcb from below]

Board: 2 copper layers, 89.6 x 85.7 mm, 91 parts (3 on the bottom side), 171 nets.

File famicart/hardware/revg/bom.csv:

Qty,Value,Footprint,References,Suggested part
1,Famicom 60-pin edge,Famicom_CardEdge_60,J1,"PCB card edge (gold fingers), no part"
4,Raspberry Pi Pico 2,RPi_Pico_SMD_Short,U1 U2 U4 U5,"hand-soldered: Akizuki 129604, 990 yen"
2,Seeed XIAO RP2350,XIAO-RP2350-Edge,U3 U6,"hand-soldered: Akizuki 129619, 1,100 yen"
30,1k x4,R_Array_Convex_4x0603,RN1 RN2 RN3 RN4 RN5 RN6 RN7 RN8 RN9 RN10 RN11 RN12 RN13 RN14 RN15 RN16 RN17 RN18 RN19 RN20 RN21 RN22 RN23 RN24 RN25 RN26 RN27 RN28 RN29 RN30,"4D03WGJ0102T5E 1k x4 0603 (LCSC C20197, JLCPCB Basic)"
6,2N7002,SOT-23,Q1 Q2 Q3 Q4 Q5 Q6,"2N7002 SOT-23 (LCSC C8545, JLCPCB Basic)"
12,2.2k,R_0603_1608Metric,R1 R3 R4 R5 R6 R7 R8 R9 R10 R15 R19 R20,"0603WAF2201T5E 2.2k 0603 (LCSC C4190, JLCPCB Basic)"
8,100k,R_0603_1608Metric,R2 R11 R12 R13 R14 R16 R17 R18,"0603WAF1003T5E 100k 0603 (LCSC C25803, JLCPCB Basic)"
9,BAV99,SOT-23,D1 D2 D3 D4 D5 D6 D7 D8 D9,"BAV99,215 SOT-23 (LCSC C2500, JLCPCB Basic)"
3,10n,C_0603_1608Metric,C1 C2 C7,"0603B103K500NT 10nF 0603 (LCSC C57112, JLCPCB Basic)"
6,B5819W,D_SOD-123,D10 D11 D12 D13 D14 D15,"B5819W SOD-123 (LCSC C8598, JLCPCB Basic)"
5,10u,C_0805_2012Metric,C3 C4 C5 C6 C8,"CL21A106KAYNNNE 10uF 0805 (LCSC C15850, JLCPCB Basic)"
1,W25Q128JVSIQ,SOIC-8_5.23x5.23mm_P1.27mm,U7,"W25Q128JVSIQ 16MB SPI flash SOIC-8 208mil (LCSC C97521, JLCPCB Basic)"
1,microSD DM3AT-SF-PEJM5,microSD_HC_Hirose_DM3AT-SF-PEJM5,J3,"hand-soldered: Akizuki 102395, 150 yen, optional"
1,RESET,SW_Push_1P1T_XKB_TS-1187A,SW1,"TS-1187A-B-A-B (LCSC C318884, JLCPCB Basic)"
1,RST/GND/LINK pads,WirePads_1x3,J2,
1,EXT/GND/3V3 pads,WirePads_1x3,J4,
